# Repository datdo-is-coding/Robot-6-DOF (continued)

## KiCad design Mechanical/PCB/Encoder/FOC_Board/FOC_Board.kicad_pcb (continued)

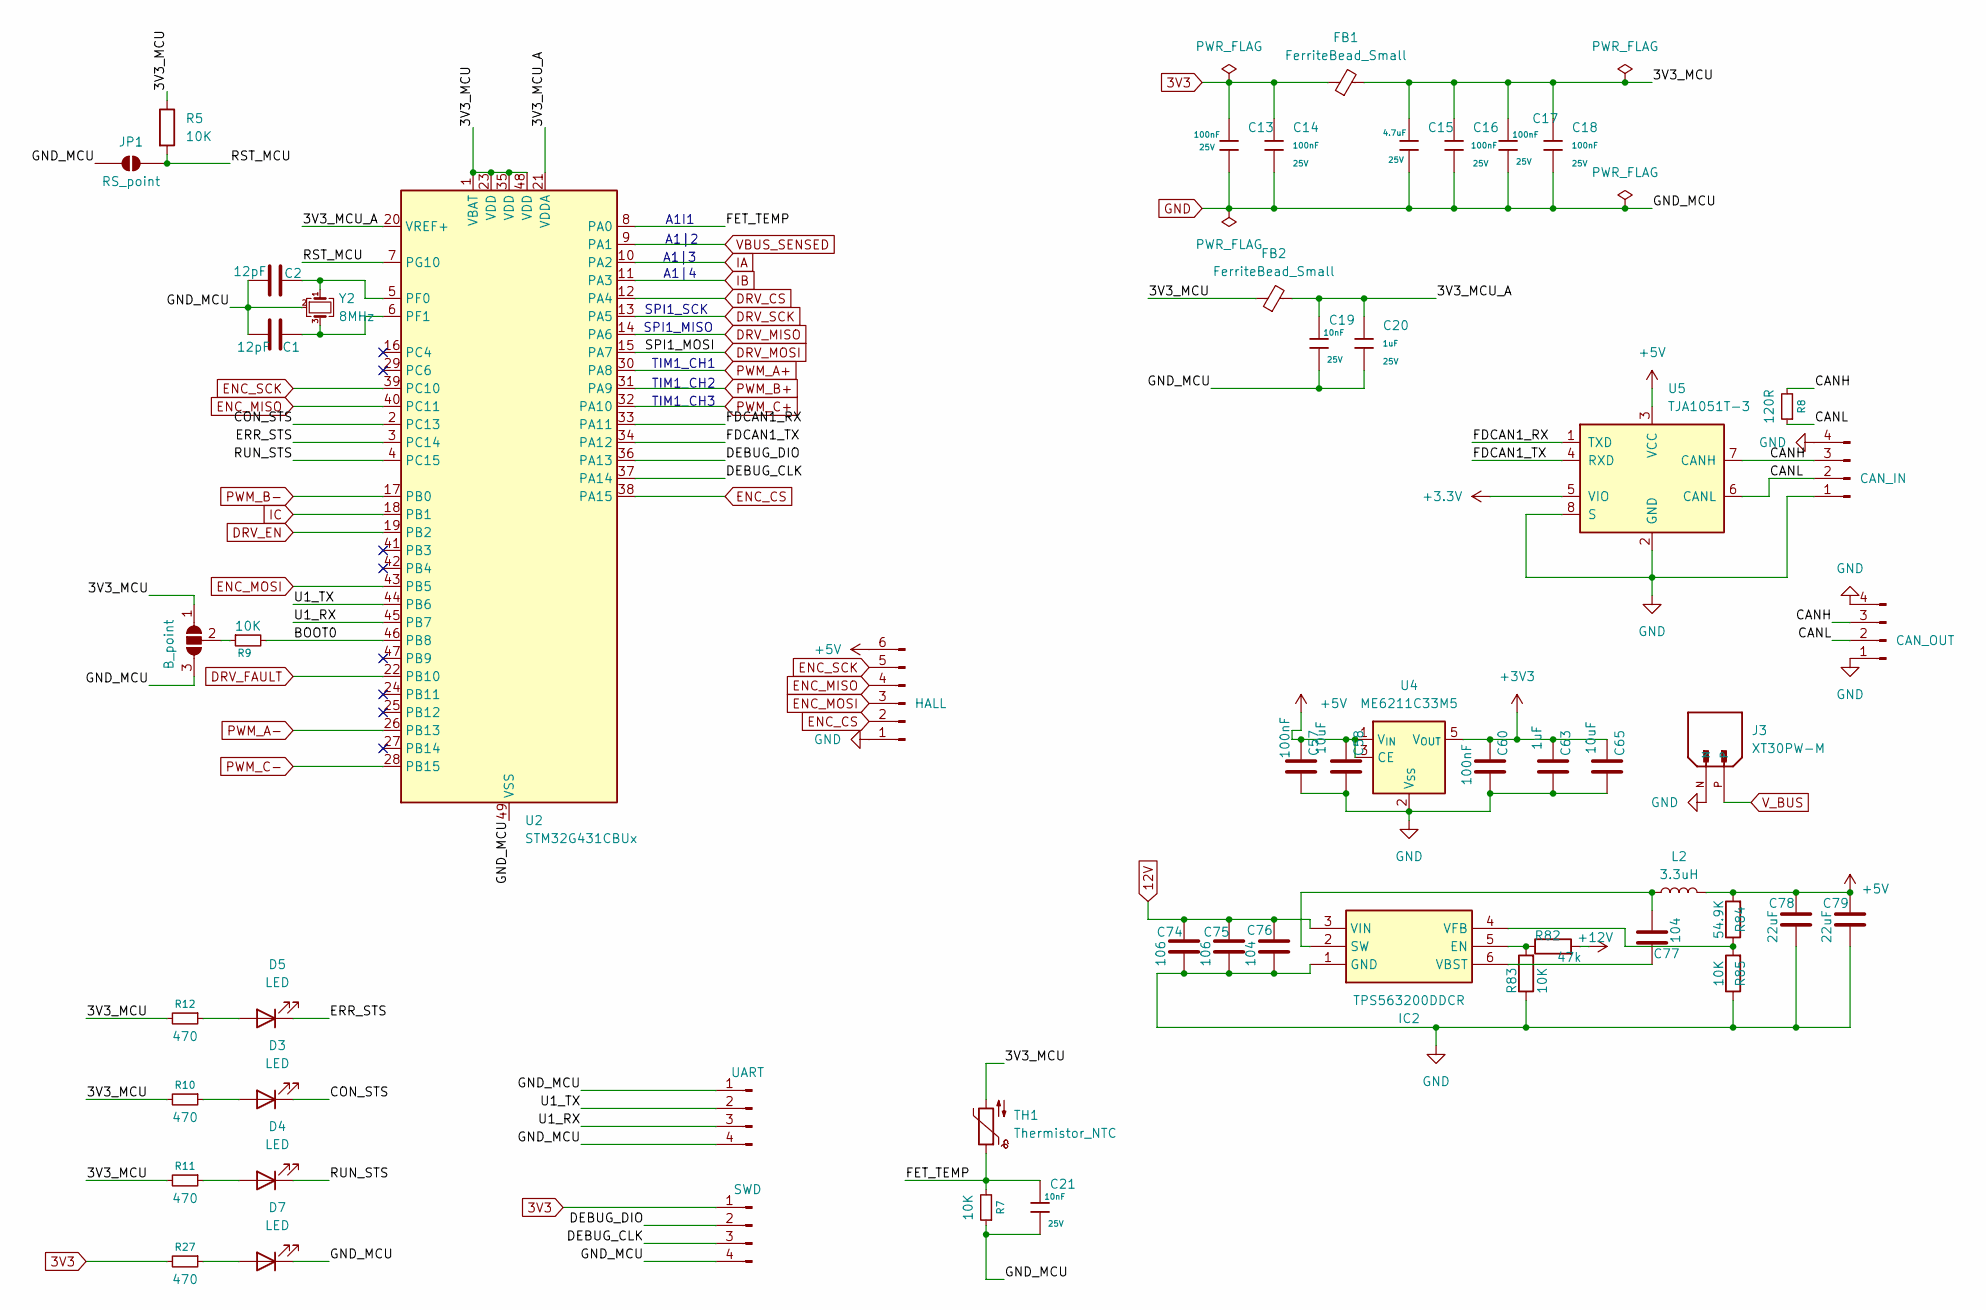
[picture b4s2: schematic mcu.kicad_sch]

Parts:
C1, C2: 12pF; C_0402_1005Metric
C13, C14, C16, C17, C18: 100nF; C_0805_2012Metric; Voltage Rated 25V; Tolerance ±10%; Part CL21A106KAYNNNE; LCSC C15850
C15: 4.7uF; C_0805_2012Metric; Voltage Rated 25V; Tolerance ±10%; Part CL21A106KAYNNNE; LCSC C15850
C19, C21: 10nF; C_0805_2012Metric; Voltage Rated 25V; Tolerance ±10%; Part CL21A106KAYNNNE; LCSC C15850
C20: 1uF; C_0805_2012Metric; Voltage Rated 25V; Tolerance ±10%; Part CL21A106KAYNNNE; LCSC C15850
C57, C60: 100nF; R_0603_1608Metric_Pad0.98x0.95mm_HandSolder
C58, C65: 10uF; R_0603_1608Metric_Pad0.98x0.95mm_HandSolder
C63: 1uF; R_0603_1608Metric_Pad0.98x0.95mm_HandSolder
C74, C75: 106; R_1206_3216Metric_Pad1.30x1.75mm_HandSolder
C76, C77: 104; R_0603_1608Metric_Pad0.98x0.95mm_HandSolder
C78, C79: 22uF; R_0603_1608Metric_Pad0.98x0.95mm_HandSolder
D3, D4, D5, D7: LED; LED_0805_2012Metric
FB1, FB2: FerriteBead_Small; L_0603_1608Metric_Pad1.05x0.95mm_HandSolder
IC2: TPS563200DDCR; SOT95P280X110-6N; Manufacturer_Part_Number TPS563200DDCR; Mouser Part Number 595-TPS563200DDCR
J1: CAN_IN; JST_GH_BM04B-GHS-TBT_1x04-1MP_P1.25mm_Vertical
J2: CAN_OUT; JST_GH_BM04B-GHS-TBT_1x04-1MP_P1.25mm_Vertical
J3: XT30PW-M; AMASS_XT30PW-M; PARTREV 1.2
J7: SWD; JST_GH_BM04B-GHS-TBT_1x04-1MP_P1.25mm_Vertical
J8: UART; JST_GH_BM04B-GHS-TBT_1x04-1MP_P1.25mm_Vertical
J9: HALL; JST_GH_BM06B-GHS-TBT_1x06-1MP_P1.25mm_Vertical
JP1: RS_point; SolderJumper-2_P1.3mm_Open_RoundedPad1.0x1.5mm
JP2: B_point; SolderJumper-3_P1.3mm_Open_RoundedPad1.0x1.5mm_NumberLabels
L2: 3.3uH; L_7.3x7.3_H3.5
R5: 10K; R_0603_1608Metric
R7, R9: 10K; R_0805_2012Metric
R8: 120R; R_0603_1608Metric
R10, R11, R12, R27: 470; R_0805_2012Metric
R82: 47k; R_0603_1608Metric_Pad0.98x0.95mm_HandSolder
R83, R85: 10K; R_0603_1608Metric_Pad0.98x0.95mm_HandSolder
R84: 54.9K; R_0603_1608Metric_Pad0.98x0.95mm_HandSolder
TH1: Thermistor_NTC; R_Axial_DIN0204_L3.6mm_D1.6mm_P1.90mm_Vertical
U2: STM32G431CBUx; QFN-48-1EP_7x7mm_P0.5mm_EP5.6x5.6mm
U4: ME6211C33M5; SOT-23-5
U5: TJA1051T-3; SOIC-8_3.9x4.9mm_P1.27mm
Y2: 8MHz; Crystal_SMD_3225-4Pin_3.2x2.5mm

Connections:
12V: C74.1, C75.1, C76.1, IC2.3 (VIN); also elsewhere on the board
+3.3V: U5.5 (VIO)
+3V3: C60.2, C63.2, C65.2, U4.5 (V_{OUT})
+5V: C57.2, C58.2, C78.1, C79.1, J9.6, L2.2, R84.2, U4.1 (V_{IN}), U4.3 (CE), U5.3 (VCC)
+12V: R82.2
/MCU/3V3_MCU_A: C19.1, C20.1, FB2.2, U2.20 (VREF+), U2.21 (VDDA)
/MCU/BOOT0: R9.2, U2.46 (PB8)
/MCU/CANH: J1.3, J2.3, R8.2, U5.7 (CANH)
/MCU/CANL: J1.2, J2.2, R8.1, U5.6 (CANL)
/MCU/CON_STS: D3.1 (K), U2.2 (PC13)
/MCU/DEBUG_CLK: J7.3, U2.37 (PA14)
/MCU/DEBUG_DIO: J7.2, U2.36 (PA13)
/MCU/ERR_STS: D5.1 (K), U2.3 (PC14)
/MCU/FDCAN1_RX: U2.33 (PA11), U5.1 (TXD)
/MCU/FDCAN1_TX: U2.34 (PA12), U5.4 (RXD)
/MCU/FET_TEMP: C21.1, R7.2, TH1.1, U2.8 (PA0)
/MCU/RST_MCU: JP1.2 (B), R5.2, U2.7 (PG10)
/MCU/RUN_STS: D4.1 (K), U2.4 (PC15)
/MCU/U1_RX: J8.3, U2.45 (PB7)
/MCU/U1_TX: J8.2, U2.44 (PB6)
DRV_CS: U2.12 (PA4); also elsewhere on the board
DRV_EN: U2.19 (PB2); also elsewhere on the board
DRV_FAULT: U2.22 (PB10); also elsewhere on the board
DRV_MISO: U2.14 (PA6); also elsewhere on the board
DRV_MOSI: U2.15 (PA7); also elsewhere on the board
DRV_SCK: U2.13 (PA5); also elsewhere on the board
ENC_CS: J9.2, U2.38 (PA15)
ENC_MISO: J9.4, U2.40 (PC11)
ENC_MOSI: J9.3, U2.43 (PB5)
ENC_SCK: J9.5, U2.39 (PC10)
GND: C1.1, C2.1, C13.2, C14.2, C15.2, C16.2, C17.2, C18.2, C19.2, C20.2, C21.2, C57.1, C58.1, C60.1, C63.1, C65.1, C74.2, C75.2, C76.2, C78.2, C79.2, D7.1 (K), IC2.1 (GND), J1.1, J1.4, J2.1, J2.4, J3.N, J7.4, J8.1, J8.4, J9.1, JP1.1 (A), JP2.3 (B), R7.1, R83.1, R85.1, U2.49 (VSS), U4.2 (V_{SS}), U5.2 (GND), U5.8 (S), Y2.2 (G), Y2.4 (G); also elsewhere on the board
IA: U2.10 (PA2); also elsewhere on the board
IB: U2.11 (PA3); also elsewhere on the board
IC: U2.18 (PB1); also elsewhere on the board
unnamed: D3.2 (A), R10.1
unnamed: D4.2 (A), R11.1
unnamed: D5.2 (A), R12.1
unnamed: D7.2 (A), R27.1
unnamed: IC2.5 (EN), R82.1, R83.2
unnamed: C77.2, IC2.2 (SW), L2.1
unnamed: C77.1, IC2.6 (VBST)
unnamed: IC2.4 (VFB), R84.1, R85.2
unnamed: JP2.2 (C), R9.1
unnamed: C2.2, U2.5 (PF0), Y2.1
unnamed: C1.2, U2.6 (PF1), Y2.3
PWM_A+: U2.30 (PA8); also elsewhere on the board
PWM_A-: U2.26 (PB13); also elsewhere on the board
PWM_B+: U2.31 (PA9); also elsewhere on the board
PWM_B-: U2.17 (PB0); also elsewhere on the board
PWM_C+: U2.32 (PA10); also elsewhere on the board
PWM_C-: U2.28 (PB15); also elsewhere on the board
VBUS_SENSED: U2.9 (PA1)
V_BUS: J3.P; also elsewhere on the board

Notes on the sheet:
A1|4
SPI1_SCK
A1|2
TIM1_CH3
TIM1_CH2
SPI1_MISO
TIM1_CH1
A1|3
A1I1

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
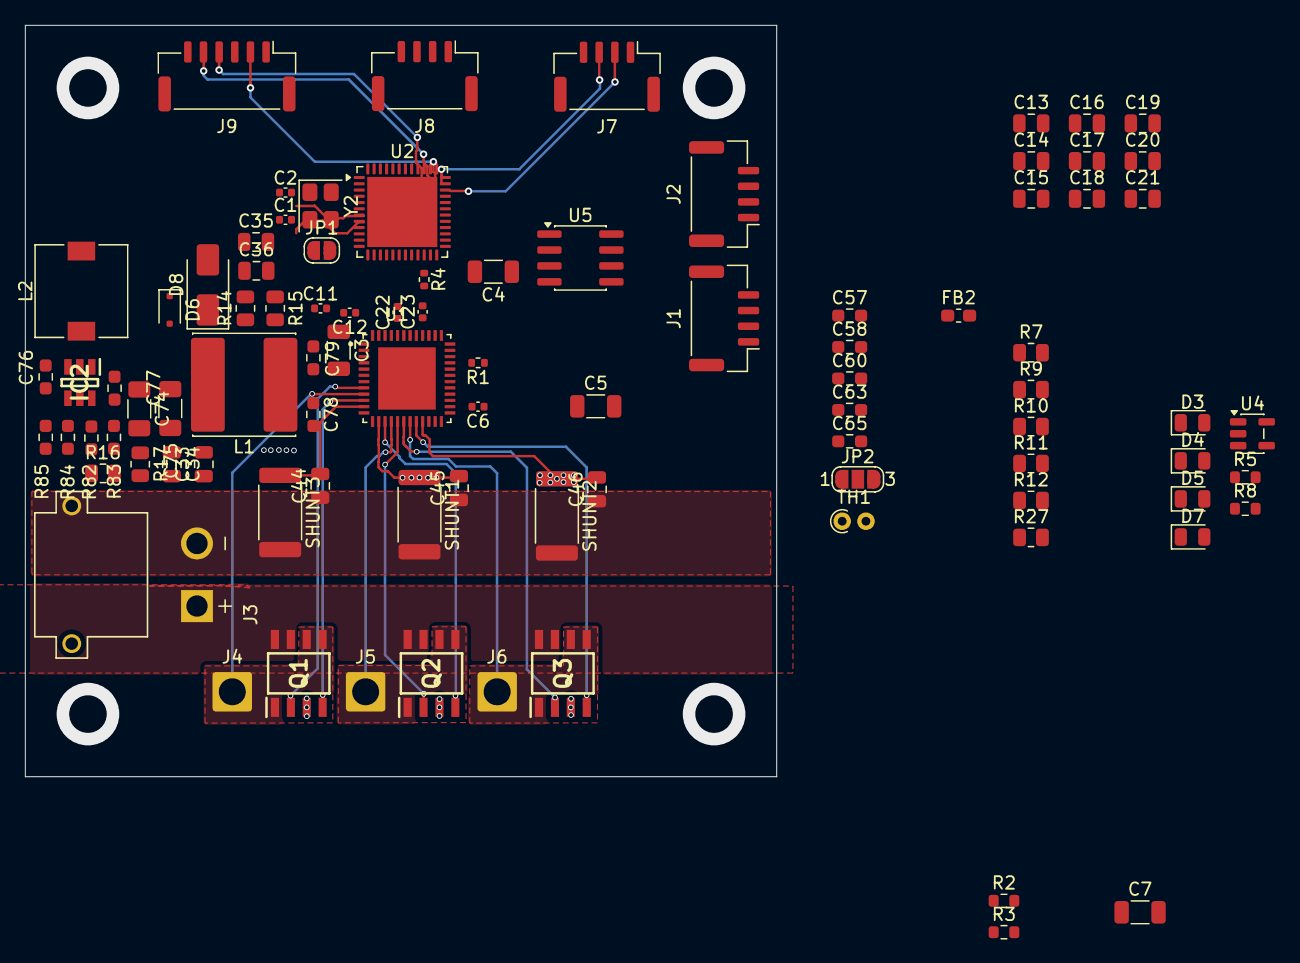
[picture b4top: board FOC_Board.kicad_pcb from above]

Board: 4 copper layers, 60.0 x 60.0 mm, 91 parts (0 on the bottom side), 76 nets.

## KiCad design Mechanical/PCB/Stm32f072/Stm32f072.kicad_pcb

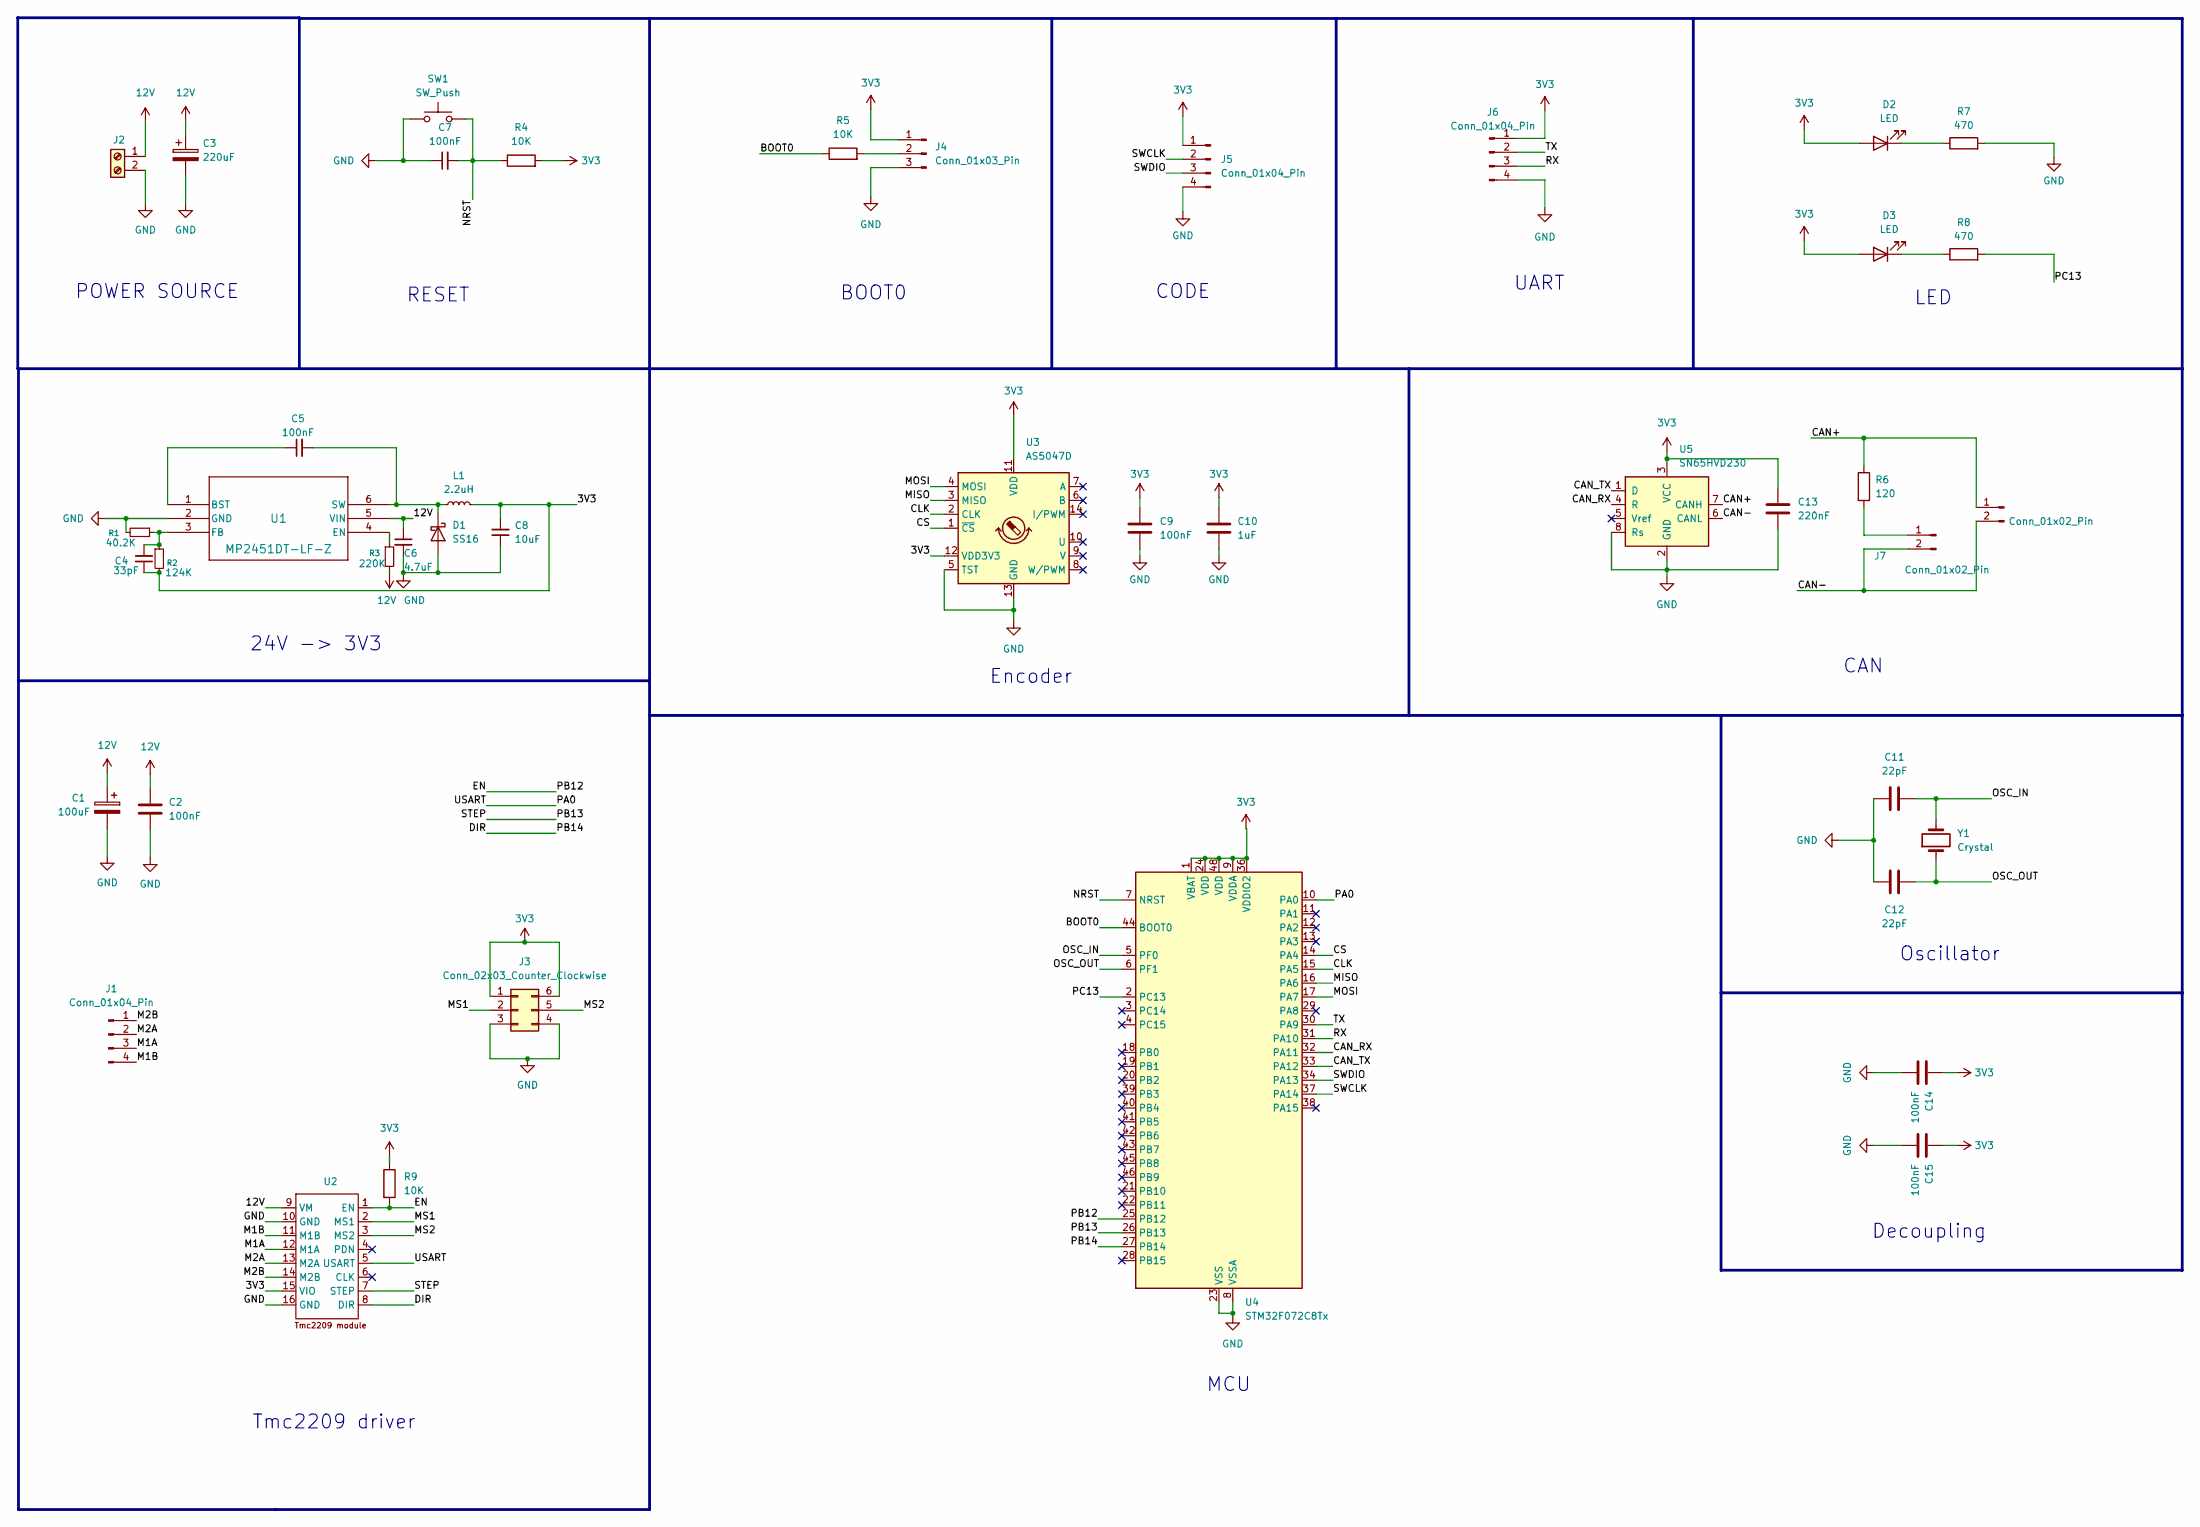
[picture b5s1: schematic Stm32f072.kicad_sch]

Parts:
C1: 100uF; CP_Elec_8x10.5
C2, C5, C7, C9, C14, C15: 100nF; C_0805_2012Metric_Pad1.18x1.45mm_HandSolder
C3: 220uF; CP_Elec_10x10.5
C4: 33pF; C_0805_2012Metric_Pad1.18x1.45mm_HandSolder
C6: 4.7uF; C_0805_2012Metric_Pad1.18x1.45mm_HandSolder
C8: 10uF; C_0805_2012Metric_Pad1.18x1.45mm_HandSolder
C10: 1uF; C_0805_2012Metric_Pad1.18x1.45mm_HandSolder
C11, C12: 22pF; C_0805_2012Metric_Pad1.18x1.45mm_HandSolder
C13: 220nF; C_0805_2012Metric_Pad1.18x1.45mm_HandSolder
D1: SS16; D_SMA
D2, D3: LED; LED_0805_2012Metric_Pad1.15x1.40mm_HandSolder
J1: Conn_01x04_Pin; PinHeader_1x04_P2.54mm_Horizontal
J2: Screw_Terminal_01x02; TerminalBlock_Phoenix_MKDS-1,5-2-5.08_1x02_P5.08mm_Horizont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
J3: Conn_02x03_Counter_Clockwise; PinHeader_2x03_P2.54mm_Vertical
J4: Conn_01x03_Pin; PinHeader_1x03_P2.54mm_Vertical
J5, J6: Conn_01x04_Pin; PinHeader_1x04_P2.54mm_Vertical
J7, J8: Conn_01x02_Pin; PinHeader_1x02_P2.54mm_Vertical
L1: 2.2uH; L_Wurth_WE-LQSH-3012
R1: 40.2K; R_0805_2012Metric_Pad1.20x1.40mm_HandSolder
R2: 124K; R_0805_2012Metric_Pad1.20x1.40mm_HandSolder
R3: 220K; R_0805_2012Metric_Pad1.20x1.40mm_HandSolder
R4, R5, R9: 10K; R_0805_2012Metric_Pad1.20x1.40mm_HandSolder
R6: 120; R_0805_2012Metric_Pad1.20x1.40mm_HandSolder
R7, R8: 470; R_0805_2012Metric_Pad1.20x1.40mm_HandSolder
SW1: SW_Push; SW_Tactile_SPST_NO_Straight_CK_PTS636Sx25SMTRLFS
U1: MP2451DT-LF-Z; SOT23-6_MP2451_MNP-M
U2: Tmc2209 module
U3: AS5047D; TSSOP-14_4.4x5mm_P0.65mm
U4: STM32F072C8Tx; LQFP-48_7x7mm_P0.5mm
U5: SN65HVD230; SOIC-8_3.9x4.9mm_P1.27mm
Y1: Crystal; Crystal_HC49-4H_Vertical

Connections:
3V3: C4.1, C8.2, C9.1, C10.1, C13.1, C14.1, C15.1, D2.2 (A), D3.2 (A), J3.1, J3.6, J4.1, J5.1, J6.1, L1.2, R2.2, R4.2, R9.1, U2.15 (VIO), U3.11 (VDD), U3.12 (VDD3V3), U4.1 (VBAT), U4.9 (VDDA), U4.24 (VDD), U4.36 (VDDIO2), U4.48 (VDD), U5.3 (VCC)
12V: C1.1, C2.1, C3.1, C6.1, J2.1, R3.2, U1.5 (VIN), U2.9 (VM)
/BOOT0: R5.1, U4.44 (BOOT0)
/CAN+: J8.1, R6.1, U5.7 (CANH)
/CAN-: J7.2, J8.2, U5.6 (CANL)
/CAN_RX: U4.32 (PA11), U5.4 (R)
/CAN_TX: U4.33 (PA12), U5.1 (D)
/CLK: U3.2 (CLK), U4.15 (PA5)
/CS: U3.1 (~CS), U4.14 (PA4)
/DIR: U2.8 (DIR), U4.27 (PB14)
/EN: R9.2, U2.1 (EN), U4.25 (PB12)
/M1A: J1.3, U2.12 (M1A)
/M1B: J1.4, U2.11 (M1B)
/M2A: J1.2, U2.13 (M2A)
/M2B: J1.1, U2.14 (M2B)
/MISO: U3.3 (MISO), U4.16 (PA6)
/MOSI: U3.4 (MOSI), U4.17 (PA7)
/MS1: J3.2, U2.2 (MS1)
/MS2: J3.5, U2.3 (MS2)
/NRST: C7.2, R4.1, SW1.2, U4.7 (NRST)
/OSC_IN: C11.2, U4.5 (PF0), Y1.2
/OSC_OUT: C12.2, U4.6 (PF1), Y1.1
/PA0: U2.5 (USART), U4.10 (PA0)
/PB13: U2.7 (STEP), U4.26 (PB13)
/PC13: R8.2, U4.2 (PC13)
/RX: J6.3, U4.31 (PA10)
/SWCLK: J5.2, U4.37 (PA14)
/SWDIO: J5.3, U4.34 (PA13)
/TX: J6.2, U4.30 (PA9)
GND: C1.2, C2.2, C3.2, C6.2, C7.1, C8.1, C9.2, C10.2, C11.1, C12.1, C13.2, C14.2, C15.2, D1.2 (A), J2.2, J3.3, J3.4, J4.3, J5.4, J6.4, R1.2, R7.2, SW1.1, U1.2 (GND), U2.10 (GND), U2.16 (GND), U3.5 (TST), U3.13 (GND), U4.8 (VSSA), U4.23 (VSS), U4.35 (VSS), U4.47 (VSS), U5.2 (GND), U5.8 (Rs)
unnamed: C5.2, D1.1 (K), L1.1, U1.6 (SW)
unnamed: D2.1 (K), R7.1
unnamed: D3.1 (K), R8.1
unnamed: J4.2, R5.2
unnamed: J7.1, R6.2
unnamed: C5.1, U1.1 (BST)
unnamed: R3.1, U1.4 (EN)
unnamed: C4.2, R1.1, R2.1, U1.3 (FB)

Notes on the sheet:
Oscillator
BOOT0
Encoder
RESET
POWER SOURCE
LED
CODE
Decoupling
MCU
24V -> 3V3
UART
Tmc2209 driver
CAN

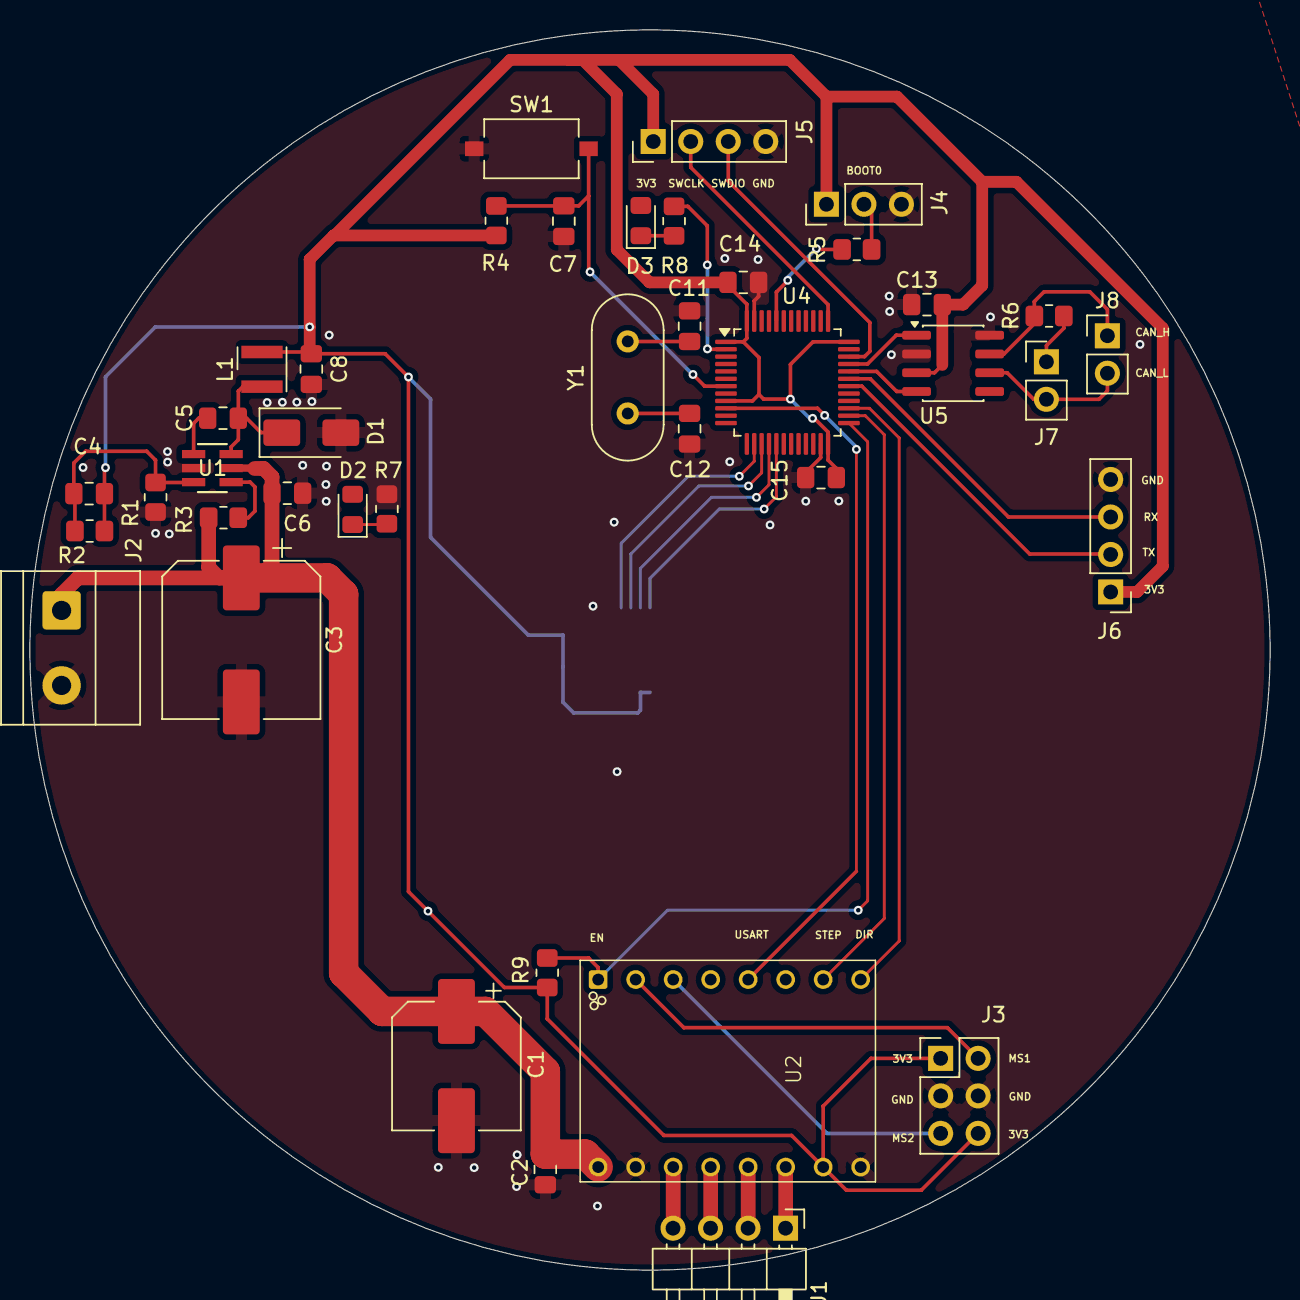
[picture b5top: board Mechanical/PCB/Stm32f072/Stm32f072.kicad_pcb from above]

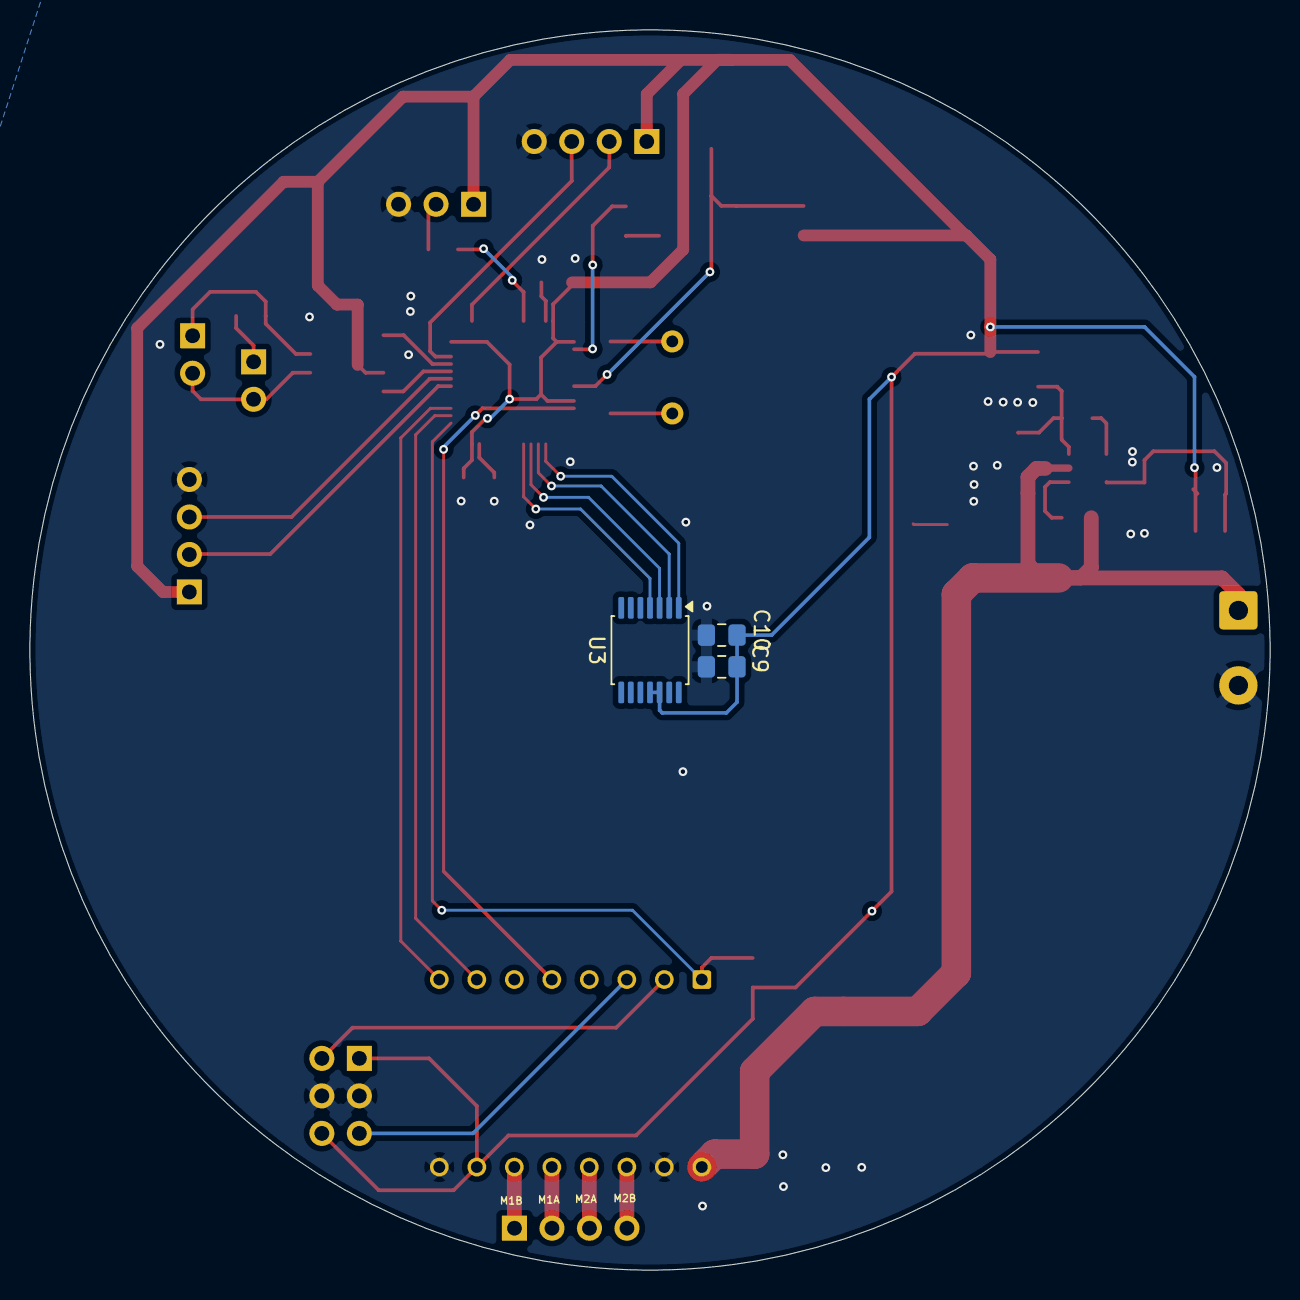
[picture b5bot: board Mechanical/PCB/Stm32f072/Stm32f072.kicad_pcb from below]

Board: 2 copper layers, 84.0 x 84.0 mm, 43 parts (3 on the bottom side), 38 nets.

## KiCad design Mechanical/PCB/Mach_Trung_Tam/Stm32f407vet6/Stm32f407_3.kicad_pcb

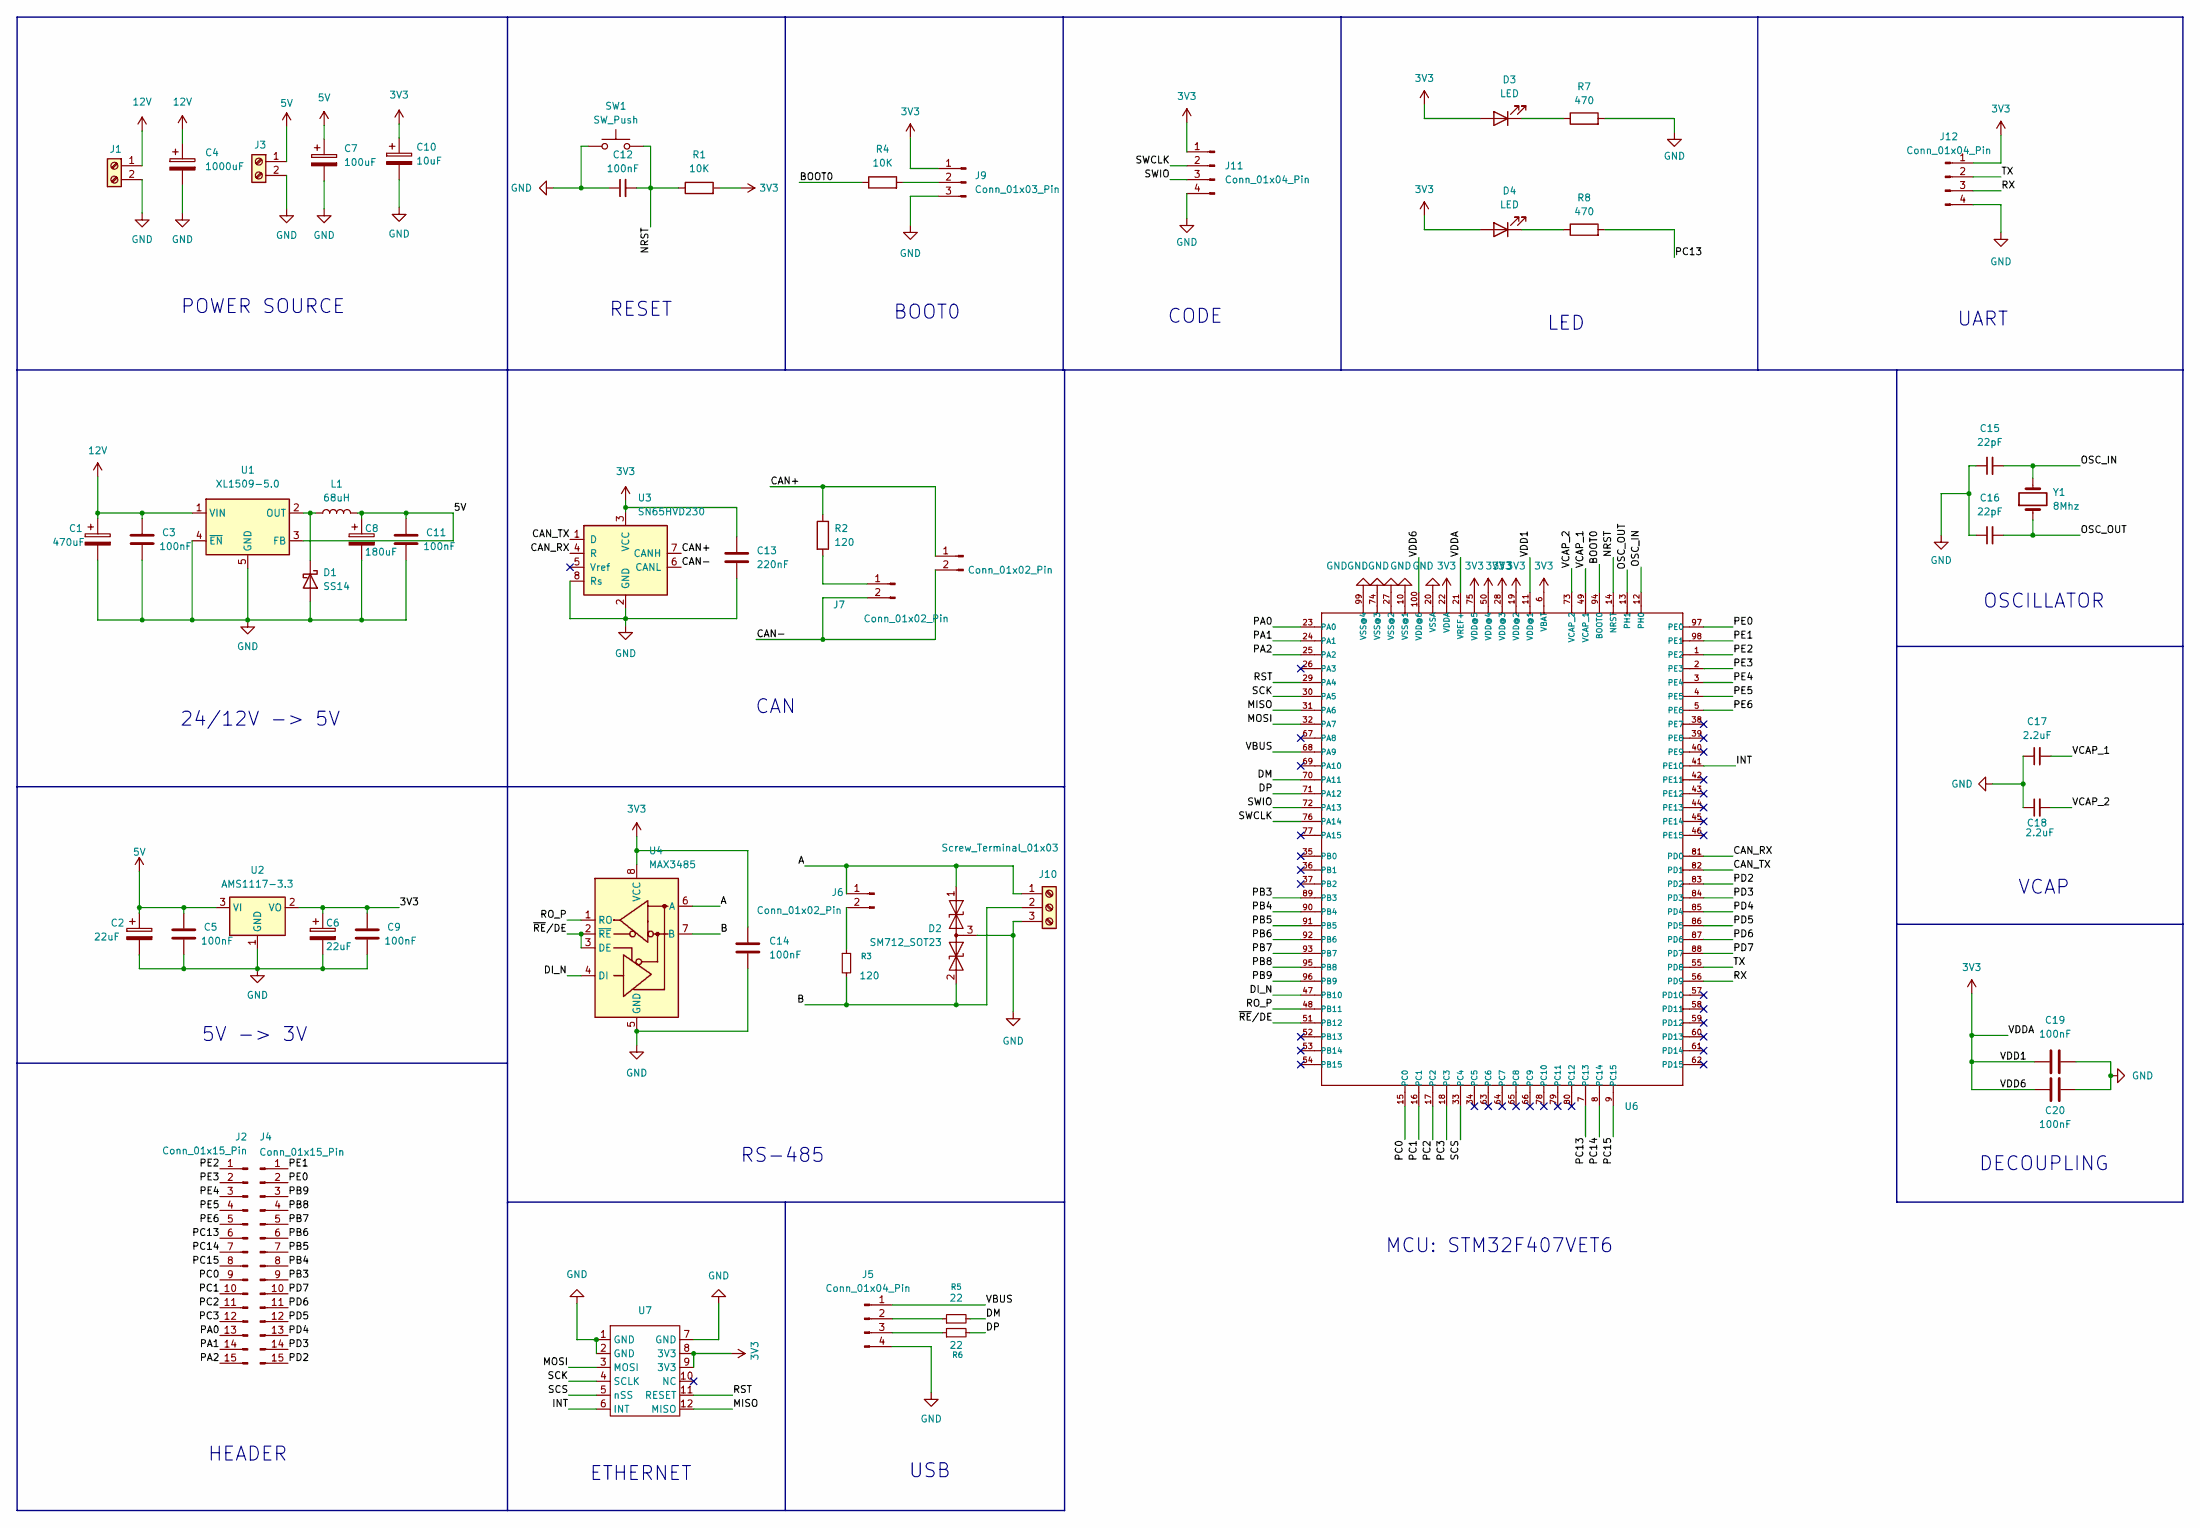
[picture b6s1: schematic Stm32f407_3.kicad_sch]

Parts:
C1: 470uF; CP_Elec_8x10.5
C2, C6: 22uF; CP_Elec_6.3x5.2
C3, C5, C9, C11, C12, C14, C19, C20: 100nF; C_0805_2012Metric_Pad1.18x1.45mm_HandSolder
C4: 1000uF; CP_Elec_12.5x13.5
C7: 100uF; CP_Elec_6.3x5.4
C8: 180uF; CP_Elec_8x10
C10: 10uF; CP_Elec_4x5.4
C13: 220nF; C_0805_2012Metric_Pad1.18x1.45mm_HandSolder
C15, C16: 22pF; C_0805_2012Metric_Pad1.18x1.45mm_HandSolder
C17, C18: 2.2uF; C_0805_2012Metric_Pad1.18x1.45mm_HandSolder
D1: SS14; D_SMA
D2: SM712_SOT23; SOT-23
D3, D4: LED; LED_0805_2012Metric_Pad1.15x1.40mm_HandSolder
J1: Screw_Terminal_01x02; TerminalBlock_Phoenix_MKDS-1,5-2-5.08_1x02_P5.08mm_Horizont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
J2, J4: Conn_01x15_Pin; PinHeader_1x15_P2.54mm_Vertical
J3: Screw_Terminal_01x02; TerminalBlock_Phoenix_PT-1,5-2-3.5-H_1x02_P3.50mm_Horizontal
J5, J11, J12: Conn_01x04_Pin; PinHeader_1x04_P2.54mm_Vertical
J6, J7, J8: Conn_01x02_Pin; PinHeader_1x02_P2.54mm_Vertical
J9: Conn_01x03_Pin; PinHeader_1x03_P2.54mm_Vertical
J10: Screw_Terminal_01x03; TerminalBlock_Phoenix_PT-1,5-3-3.5-H_1x03_P3.50mm_Horizontal
L1: 68uH; L_0805_2012Metric_Pad1.05x1.20mm_HandSolder
R1, R4: 10K; R_0805_2012Metric_Pad1.20x1.40mm_HandSolder
R2, R3: 120; R_0805_2012Metric_Pad1.20x1.40mm_HandSolder
R5, R6: 22; R_0805_2012Metric_Pad1.20x1.40mm_HandSolder
R7, R8: 470; R_0805_2012Metric_Pad1.20x1.40mm_HandSolder
SW1: SW_Push; SW_Tactile_SPST_NO_Straight_CK_PTS636Sx25SMTRLFS
U1: XL1509-5.0; SOIC-8_3.9x4.9mm_P1.27mm
U2: AMS1117-3.3; SOT-223-3_TabPin2
U3: SN65HVD230; SOIC-8_3.9x4.9mm_P1.27mm
U4: MAX3485; SOIC-8_3.9x4.9mm_P1.27mm
U6: STM32F407VET6-LQFP100; LQFP100-0.5-13.8X13.8MM; MPN STM32F407VET6
U7: W5550 module
Y1: 8Mhz; Crystal_HC49-U_Vertical

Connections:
3V3: C6.1, C9.1, C10.1, C13.1, C14.2, C19.2, C20.2, D3.2 (A), D4.2 (A), J9.1, J11.1, J12.1, R1.2, U2.2 (VO), U3.3 (VCC), U4.8 (VCC), U6.6 (VBAT), U6.11 (VDD@1), U6.19 (VDD@2), U6.21 (VREF+), U6.22 (VDDA), U6.28 (VDD@3), U6.50 (VDD@4), U6.75 (VDD@5), U6.100 (VDD@6), U7.8 (3V3), U7.9 (3V3)
5V: C2.1, C5.1, C7.1, C8.1, C11.1, J3.1, L1.2, U1.3 (FB), U2.3 (VI)
12V: C1.1, C3.1, C4.1, J1.1, U1.1 (VIN)
/A: D2.1 (A1), J6.1, J10.1, U4.6 (A)
/B: D2.2 (A2), J10.2, R3.2, U4.7 (B)
/BOOT0: R4.1, U6.94 (BOOT0)
/CAN+: J8.1, R2.1, U3.7 (CANH)
/CAN-: J7.2, J8.2, U3.6 (CANL)
/CAN_RX: U3.4 (R), U6.81 (PD0)
/CAN_TX: U3.1 (D), U6.82 (PD1)
/DI_N: U4.4 (DI), U6.47 (PB10)
/DM: R5.2, U6.70 (PA11)
/DP: R6.2, U6.71 (PA12)
/INT: U6.41 (PE10), U7.6 (INT)
/MISO: U6.31 (PA6), U7.12 (MISO)
/MOSI: U6.32 (PA7), U7.3 (MOSI)
/NRST: C12.2, R1.1, SW1.2, U6.14 (NRST)
/OSC_IN: C15.2, U6.12 (PH0), Y1.2
/OSC_OUT: C16.2, U6.13 (PH1), Y1.1
/PA0: J2.13, U6.23 (PA0)
/PA1: J2.14, U6.24 (PA1)
/PA2: J2.15, U6.25 (PA2)
/PB3: J4.9, U6.89 (PB3)
/PB4: J4.8, U6.90 (PB4)
/PB5: J4.7, U6.91 (PB5)
/PB6: J4.6, U6.92 (PB6)
/PB7: J4.5, U6.93 (PB7)
/PB8: J4.4, U6.95 (PB8)
/PB9: J4.3, U6.96 (PB9)
/PC0: J2.9, U6.15 (PC0)
/PC1: J2.10, U6.16 (PC1)
/PC2: J2.11, U6.17 (PC2)
/PC3: J2.12, U6.18 (PC3)
/PC13: J2.6, R8.2, U6.7 (PC13)
/PC14: J2.7, U6.8 (PC14)
/PC15: J2.8, U6.9 (PC15)
/PD2: J4.15, U6.83 (PD2)
/PD3: J4.14, U6.84 (PD3)
/PD4: J4.13, U6.85 (PD4)
/PD5: J4.12, U6.86 (PD5)
/PD6: J4.11, U6.87 (PD6)
/PD7: J4.10, U6.88 (PD7)
/PE0: J4.2, U6.97 (PE0)
/PE1: J4.1, U6.98 (PE1)
/PE2: J2.1, U6.1 (PE2)
/PE3: J2.2, U6.2 (PE3)
/PE4: J2.3, U6.3 (PE4)
/PE5: J2.4, U6.4 (PE5)
/PE6: J2.5, U6.5 (PE6)
/RO_P: U4.1 (RO), U6.48 (PB11)
/RST: U6.29 (PA4), U7.11 (RESET)
/RX: J12.3, U6.56 (PD9)
/SCK: U6.30 (PA5), U7.4 (SCLK)
/SCS: U6.33 (PC4), U7.5 (nSS)
/SWCLK: J11.2, U6.76 (PA14)
/SWIO: J11.3, U6.72 (PA13)
/TX: J12.2, U6.55 (PD8)
/VBUS: J5.1, U6.68 (PA9)
/VCAP_1: C17.2, U6.49 (VCAP_1)
/VCAP_2: C18.2, U6.73 (VCAP_2)
/~RE/DE: U4.2 (~RE), U4.3 (DE), U6.51 (PB12)
GND: C1.2, C2.2, C3.2, C4.2, C5.2, C6.2, C7.2, C8.2, C9.2, C10.2, C11.2, C12.1, C13.2, C14.1, C15.1, C16.1, C17.1, C18.1, C19.1, C20.1, D1.2 (A), D2.3 (common), J1.2, J3.2, J5.4, J9.3, J10.3, J11.4, J12.4, R7.2, SW1.1, U1.4 (~EN), U1.5 (GND), U1.6 (GND), U1.7 (GND), U1.8 (GND), U2.1 (GND), U3.2 (GND), U3.8 (Rs), U4.5 (GND), U6.10 (VSS@1), U6.20 (VSSA), U6.27 (VSS@2), U6.74 (VSS@3), U6.99 (VSS@4), U7.1 (GND), U7.2 (GND), U7.7 (GND)
unnamed: D1.1 (K), L1.1, U1.2 (OUT)
unnamed: D3.1 (K), R7.1
unnamed: D4.1 (K), R8.1
unnamed: J5.2, R5.1
unnamed: J5.3, R6.1
unnamed: J6.2, R3.1
unnamed: J7.1, R2.2
unnamed: J9.2, R4.2

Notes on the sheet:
DECOUPLING
LED
CAN
CODE
OSCILLATOR
POWER SOURCE
MCU: STM32F407VET6
BOOT0
VCAP
RS-485
HEADER
UART
RESET
24/12V -> 5V
ETHERNET
USB
5V -> 3V

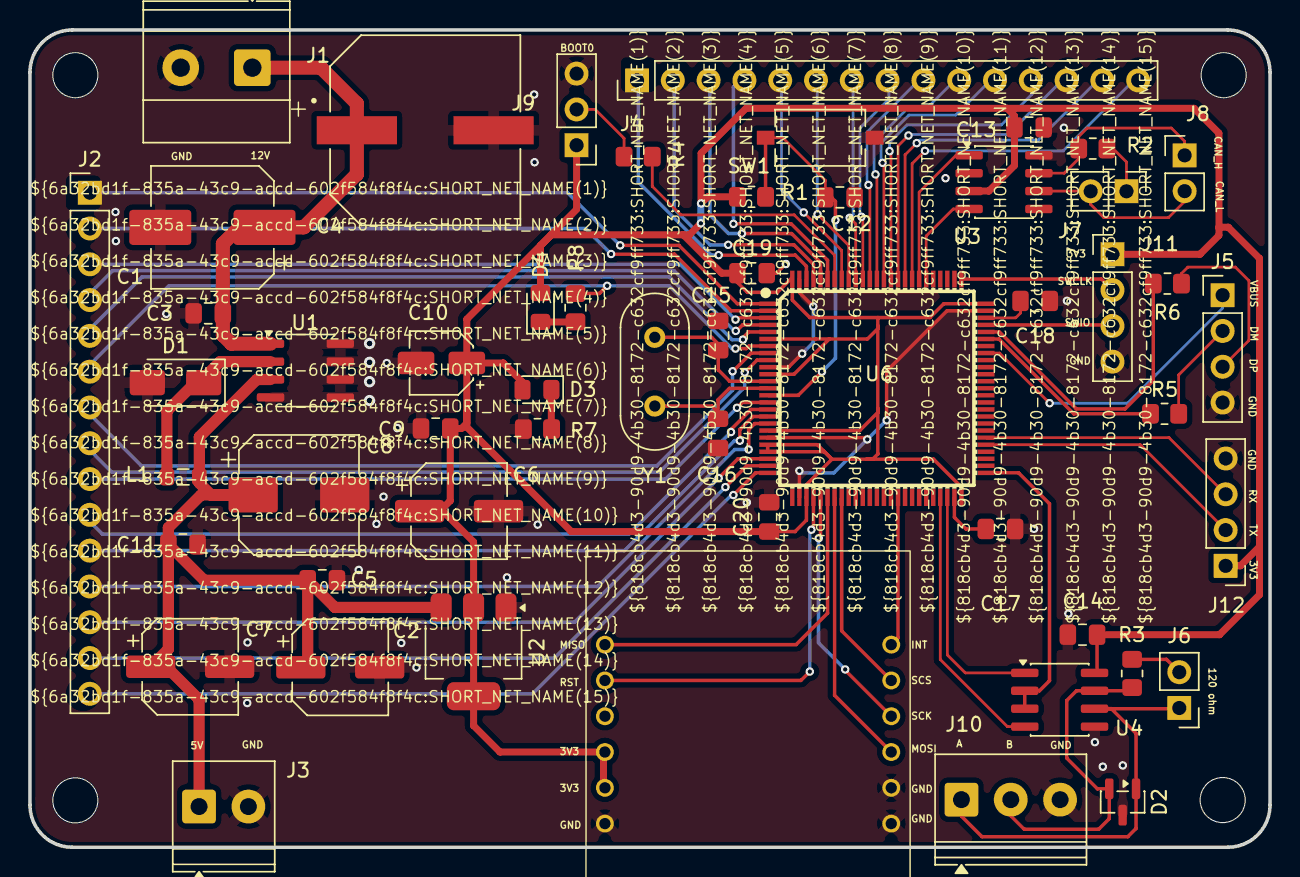
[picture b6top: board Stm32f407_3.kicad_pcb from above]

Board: 2 copper layers, 88.0 x 58.0 mm, 53 parts (0 on the bottom side), 70 nets.
